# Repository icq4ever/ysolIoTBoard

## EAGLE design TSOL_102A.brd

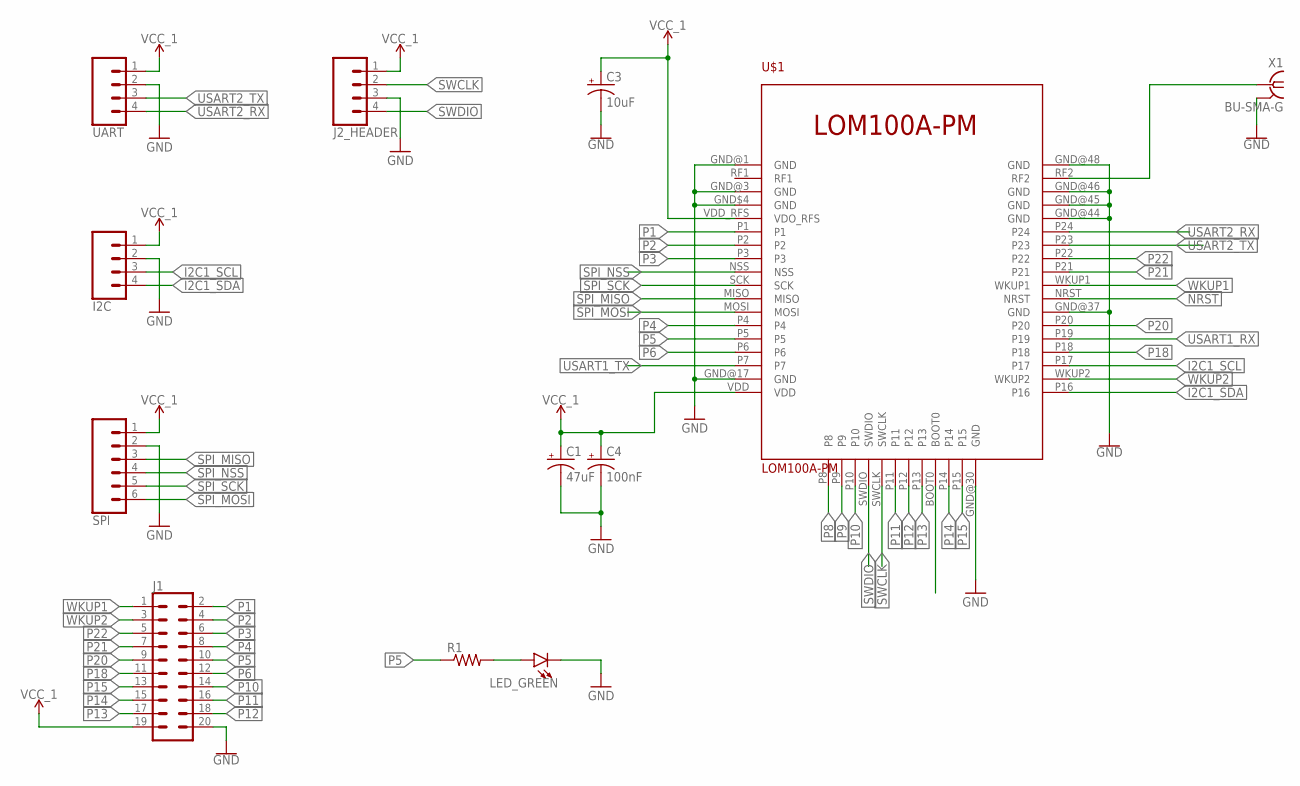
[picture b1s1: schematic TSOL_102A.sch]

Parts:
C1: 47uF; CPOL-RADIAL-5MM-10MM-KIT
C3: 10uF; CPOL-RADIAL-5MM-10MM-KIT
C4: 100nF; CPOL-RADIAL-5MM-10MM-KIT
I2C: CONN_04LONGPADS; 1X04_LONGPADS
J1: CONN_10X2; 2X10
J2_HEADER: CONN_04LONGPADS; 1X04_LONGPADS
LED_GREEN: LED5MM; LED_5MM
R1: R-US_0204/7; 0204/7
SPI: CONN_06LONGPADS; 1X06_LONGPADS
U$1: LOM100A-PM
UART: CONN_04LONGPADS; 1X04_LONGPADS
X1: BU-SMA-G

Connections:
GND: C1.-, C3.-, C4.-, I2C.2, J1.20, J2_HEADER.3, LED_GREEN.K (C), SPI.2, U$1.GND$4 (GND), U$1.GND@1 (GND), U$1.GND@3 (GND), U$1.GND@17 (GND), U$1.GND@30 (GND), U$1.GND@37 (GND), U$1.GND@44 (GND), U$1.GND@45 (GND), U$1.GND@46 (GND), U$1.GND@48 (GND), UART.2, X1.2, X1.3 (2), X1.4 (2), X1.5 (2)
I2C1_SCL: I2C.3, U$1.P17
I2C1_SDA: I2C.4, U$1.P16
unnamed: U$1.RF2, X1.1
unnamed: LED_GREEN.A, R1.2
NRST: U$1.NRST
P1: J1.2, U$1.P1
P2: J1.4, U$1.P2
P3: J1.6, U$1.P3
P4: J1.8, U$1.P4
P5: J1.10, R1.1, U$1.P5
P6: J1.12, U$1.P6
P8: U$1.P8
P9: U$1.P9
P10: J1.14, U$1.P10
P11: J1.16, U$1.P11
P12: J1.18, U$1.P12
P13: J1.17, U$1.P13
P14: J1.15, U$1.P14
P15: J1.13, U$1.P15
P18: J1.11, U$1.P18
P20: J1.9, U$1.P20
P21: J1.7, U$1.P21
P22: J1.5, U$1.P22
SPI_MISO: SPI.3, U$1.MISO
SPI_MOSI: SPI.6, U$1.MOSI
SPI_NSS: SPI.4, U$1.NSS
SPI_SCK: SPI.5, U$1.SCK
SWCLK: J2_HEADER.2, U$1.SWCLK
SWDIO: J2_HEADER.4, U$1.SWDIO
USART1_RX: U$1.P19
USART1_TX: U$1.P7
USART2_RX: U$1.P24, UART.4
USART2_TX: U$1.P23, UART.3
VCC_1: C1.+, C3.+, C4.+, I2C.1, J1.19, J2_HEADER.1, SPI.1, U$1.VDD, U$1.VDD_RFS (VDO_RFS), UART.1
WKUP1: J1.1, U$1.WKUP1
WKUP2: J1.3, U$1.WKUP2

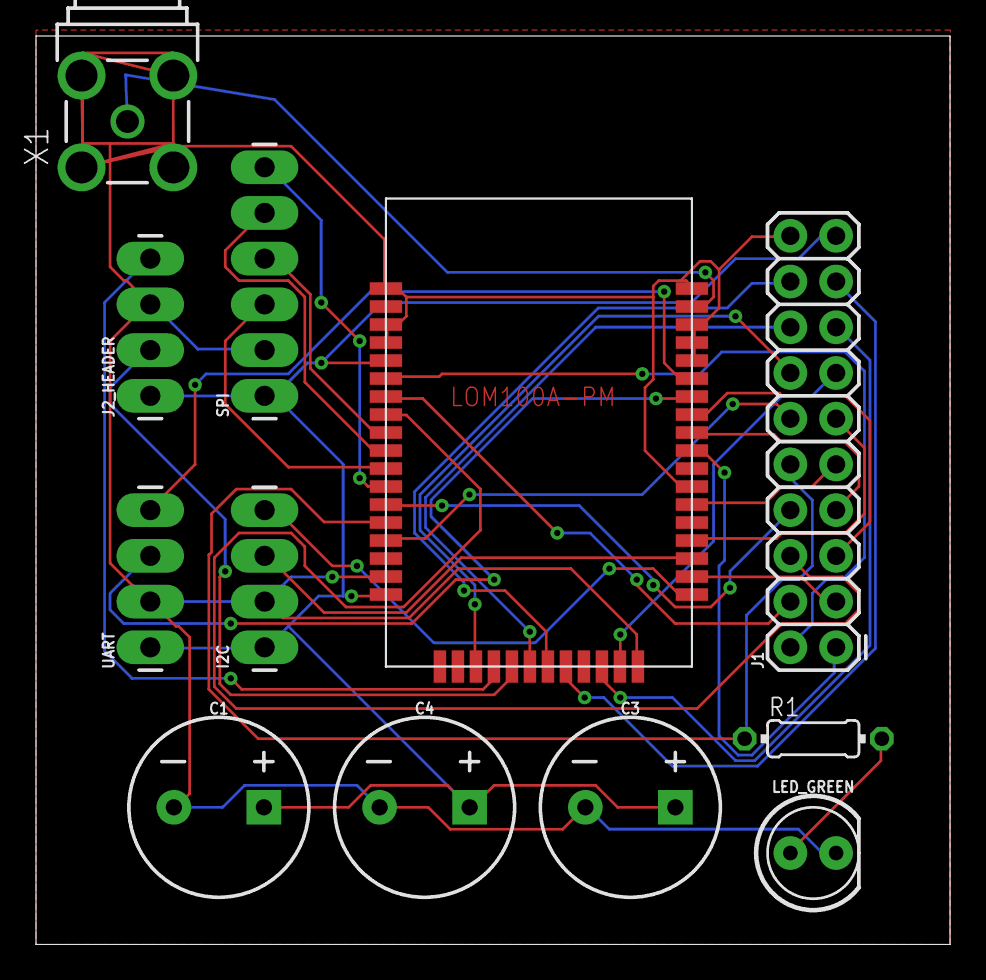
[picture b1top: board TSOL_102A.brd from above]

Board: 2 copper layers, 50.8 x 50.5 mm, 12 parts (0 on the bottom side), 32 nets.

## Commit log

2018-05-13 schmetic added
2018-05-13 library added
2018-05-13 sch brd updated

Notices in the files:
parts and their libraries:
SparkFun-Capacitors: Licensing: Creative Commons ShareAlike 4.0 International - https://creativecommons.org/licenses/by-sa/4.0
